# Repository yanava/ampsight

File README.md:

<h1>Ampsight - A configurable load for testing headphone amplifiers</h1>

<h2> Scope </h2>

Ampsight is a configurable load for testing the power output of headphone amplifiers. 

<h2> Key goals </h2>

The design goals are:

* Simplicity - not even power supply is necessary
* Ease of design, maintenance and configuration - no microcontrolers or firmware
* Instrumentation is external - bring your own measurement device
* Non inductive - good resistance performance accross frequencies
* Stable over temperature - can be used with more intense loads

<h2> Thoery of operation </h2>

Board uses a resistor bank configurable by a switching element. On current REV1 this is achieved by a 7 position DIP switch, which connects several Caddock resistors in parallel. This way many resistance values are achievable. 

After connected, the resistors are routed to input connectors that interface with the amplifier to be meausred. Today two types of inputs are available: 6.35mm (1/4 inch) jack and 4.4mm Pentaconn jack

The way to operate is - using a sound source, you program a 1khz tone to be played by the amplifier. Select a desired resistance value on ampsight, measure it using a multimeter. Connect the amplifier to ampsight and using a multimeter or osciloscope, take the alternate RMS voltage and use it in conjunction with resistance to calculate the power provided by the amplifier.

<h2> Resistance values </h2>

As of REV1 the resistance values are

* 3x 30R
* 2x 75R
* 2x 330R

<h3> Resistance combination possibilities and known headphone impedances </h3>

Coming soon.

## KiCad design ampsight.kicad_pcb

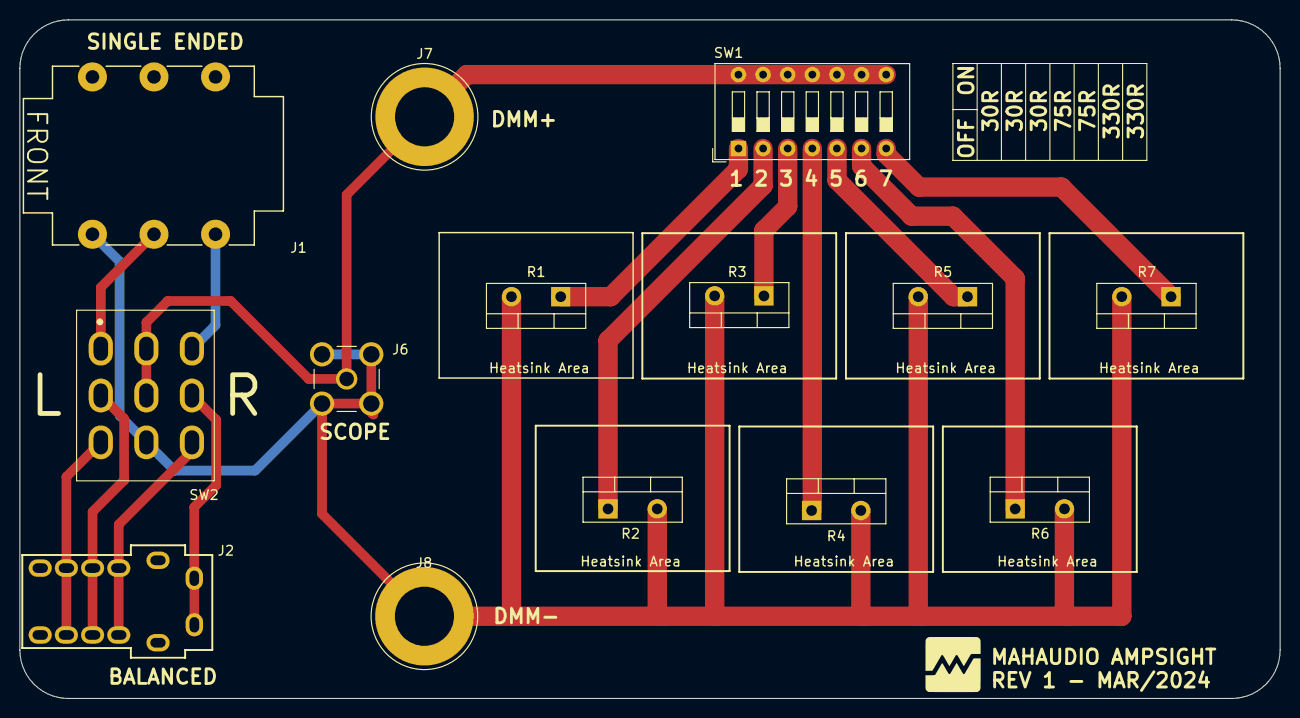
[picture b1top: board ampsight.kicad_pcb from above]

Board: 2 copper layers, 130.0 x 70.0 mm, 15 parts (0 on the bottom side), 15 nets.

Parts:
G01: LOGO
J1: AudioJack3; Jack_6.35mm_Neutrik_NMJ6HCD2_Horizontal
J2: AudioJack_Pentaconn; Jack_4.4mm_Pentaconn_NBA1-24-001_Horizontal
J6: Conn_Coaxial_Small; SMA_Amphenol_901-144_Vertical(3D)
J7, J8: Conn_01x01_Socket; Banana_Jack_1Pin(3D)
R1, R2, R3: 33R; Caddock_MP930_TO-220-2_Vertical
R4, R5: 75R; Caddock_MP930_TO-220-2_Vertical
R6: 150R; Caddock_MP930_TO-220-2_Vertical
R7: 300R; Caddock_MP930_TO-220-2_Vertical
SW1: SW_DIP_x07; SW_DIP_SPSTx07_Slide_9.78x19.96mm_W7.62mm_P2.54mm
SW2: SW_3PDT; 7000Series_3pdt_toggle_c&k

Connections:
/BAL_L_N: J2.R1 (L-), SW2.9 (A)
/BAL_L_P: J2.T (L+), SW2.6 (A)
/BAL_R_N: J2.R3 (R-), SW2.7 (C)
/BAL_R_P: J2.R2 (R+), SW2.4 (C)
/DUT_N: J1.S, J6.2 (Ext), J8.1, R1.2, R2.2, R3.2, R4.2, R5.2, R6.2, R7.2, SW2.8 (B)
/DUT_P: J6.1 (In), J7.1, SW1.8, SW1.9, SW1.10, SW1.11, SW1.12, SW1.13, SW1.14, SW2.2 (B), SW2.5 (B)
/SE_L: J1.T, SW2.3 (A)
/SE_R: J1.R, SW2.1 (C)
unnamed: R1.1, SW1.1
unnamed: R2.1, SW1.2
unnamed: R3.1, SW1.3
unnamed: R4.1, SW1.4
unnamed: R5.1, SW1.5
unnamed: R6.1, SW1.6
unnamed: R7.1, SW1.7

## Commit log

2024-04-04 Added project files of REV1
2024-04-04 Create README.md
    Basic readme
